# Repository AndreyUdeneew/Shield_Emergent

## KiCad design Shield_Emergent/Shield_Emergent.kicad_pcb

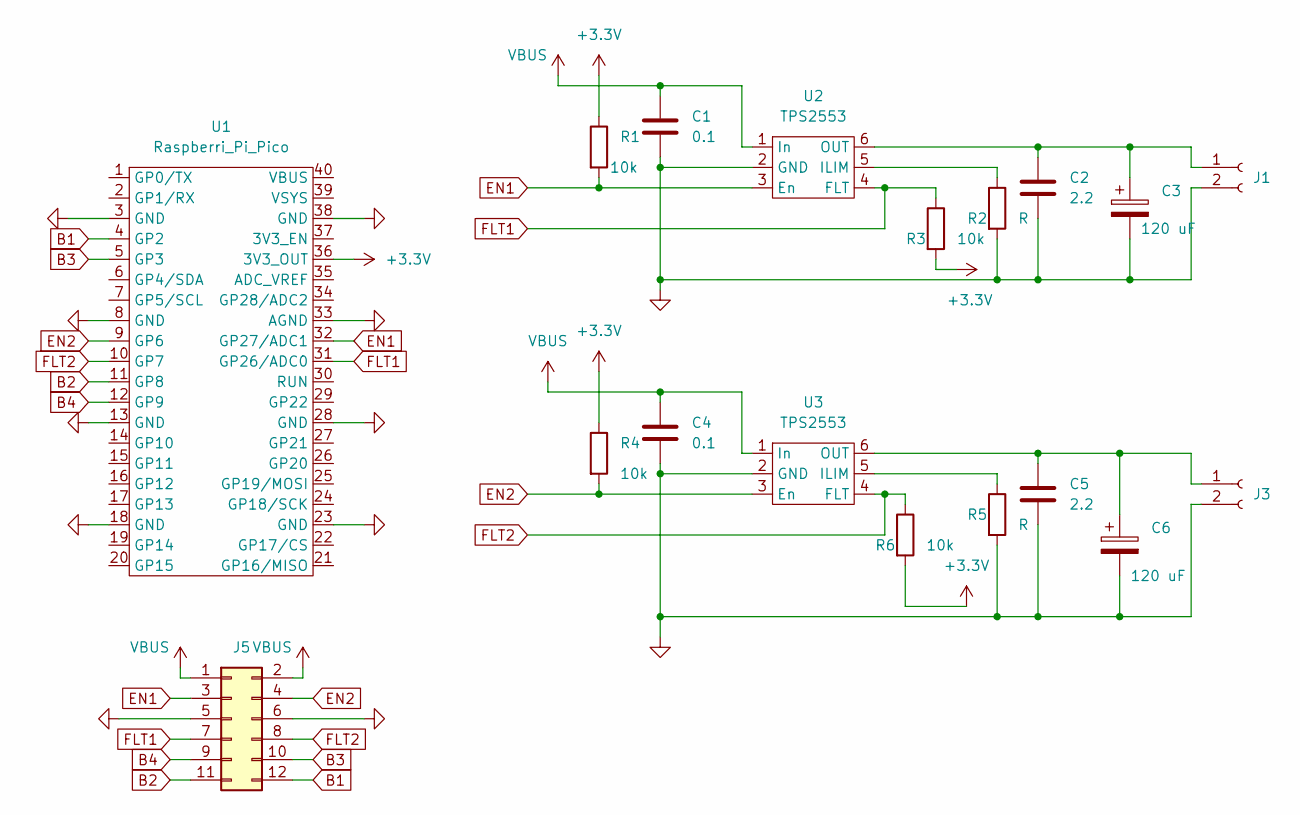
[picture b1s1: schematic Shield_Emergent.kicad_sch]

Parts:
C1, C4: 0.1; C_0603_1608Metric_Pad1.08x0.95mm_HandSolder
C2, C5: 2.2; C_0603_1608Metric_Pad1.08x0.95mm_HandSolder
C3, C6: 120 uF; CP_Radial_D6.3mm_P2.50mm
J1, J3: Conn_01x02_Female; PinSocket_1x02_P2.54mm_Vertical
J5: Conn_02x06_Odd_Even; PinHeader_2x06_P2.54mm_Vertical
R1, R3, R4, R6: 10k; R_0603_1608Metric_Pad0.98x0.95mm_HandSolder
R2, R5: R; R_0603_1608Metric_Pad0.98x0.95mm_HandSolder
U1: Raspberri_Pi_Pico; Raspberry Pi Pico
U2, U3: TPS2553; SOT-23-6_Handsoldering

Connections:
+3V3: R1.1, R3.2, R4.1, R6.2, U1.36 (3V3_OUT)
B1: J5.12, U1.4 (GP2)
B2: J5.11, U1.11 (GP8)
B3: J5.10, U1.5 (GP3)
B4: J5.9, U1.12 (GP9)
EN1: J5.3, R1.2, U1.32 (GP27/ADC1), U2.3 (En)
EN2: J5.4, R4.2, U1.9 (GP6), U3.3 (En)
FLT1: J5.7, R3.1, U1.31 (GP26/ADC0), U2.4 (FLT)
FLT2: J5.8, R6.1, U1.10 (GP7), U3.4 (FLT)
GND: C1.2, C2.2, C3.2, C4.2, C5.2, C6.2, J1.2, J3.2, J5.5, J5.6, R2.2, R5.2, U1.3 (GND), U1.8 (GND), U1.13 (GND), U1.18 (GND), U1.23 (GND), U1.28 (GND), U1.33 (AGND), U1.38 (GND), U2.2 (GND), U3.2 (GND)
unnamed: C2.1, C3.1, J1.1, U2.6 (OUT)
unnamed: C5.1, C6.1, J3.1, U3.6 (OUT)
unnamed: R2.1, U2.5 (ILIM)
unnamed: R5.1, U3.5 (ILIM)
VBUS: C1.1, C4.1, J5.1, J5.2, U2.1 (In), U3.1 (In)

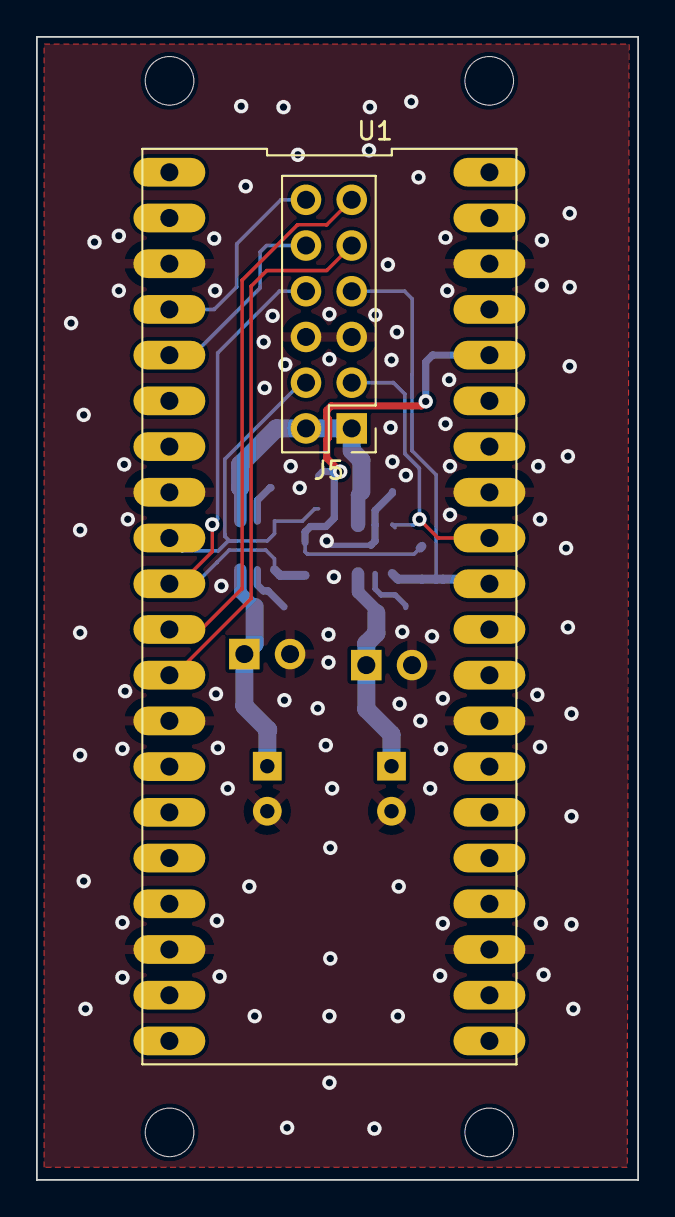
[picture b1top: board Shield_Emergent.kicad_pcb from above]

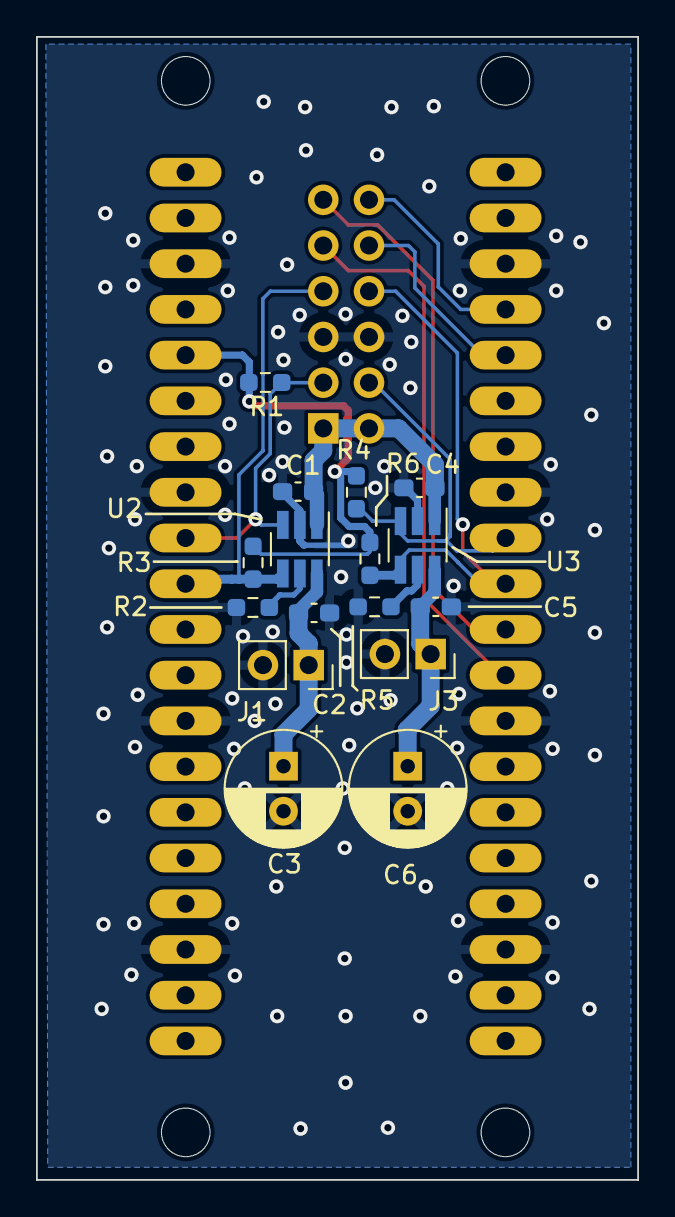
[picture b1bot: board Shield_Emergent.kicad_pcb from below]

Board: 2 copper layers, 33.4 x 63.5 mm, 18 parts (16 on the bottom side), 15 nets.

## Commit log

2022-10-18 v0.1 empty files have been created
2022-12-14 v0.1 circuit has been created
2022-12-16 v0.2 RPI_Pico symbol&pattern have been added
2022-12-16 v0.3 Circuit has been corrected
2022-12-17 v0.4 FLT nets have been added
2022-12-18 м PCB proto has been created
2022-12-18 v0.5 Partial decompoition has been completed
2022-12-19 v0.6 partially routed
2022-12-19 v0.7 Routing has been completed
2023-01-27 v0.8 silk screen has been decomposed
2023-01-30 v0.9 ready to order
2023-02-09 v1.0 Ground was corrected
2023-02-19 v1.1 Circuit was corrected, GND was enfrced
2023-02-19 v1.2 DRC was conducted
2023-03-06 v1.3 Power of RPI_PICO and Shield was splitted
2023-03-18 v1.4 four Buttons protos were added
2023-03-18 v1.5 Buttons Polarity was changed
2023-03-20 v1.6 single connector for all purposes was added
2023-03-20 v1.7 DRC was conducted
